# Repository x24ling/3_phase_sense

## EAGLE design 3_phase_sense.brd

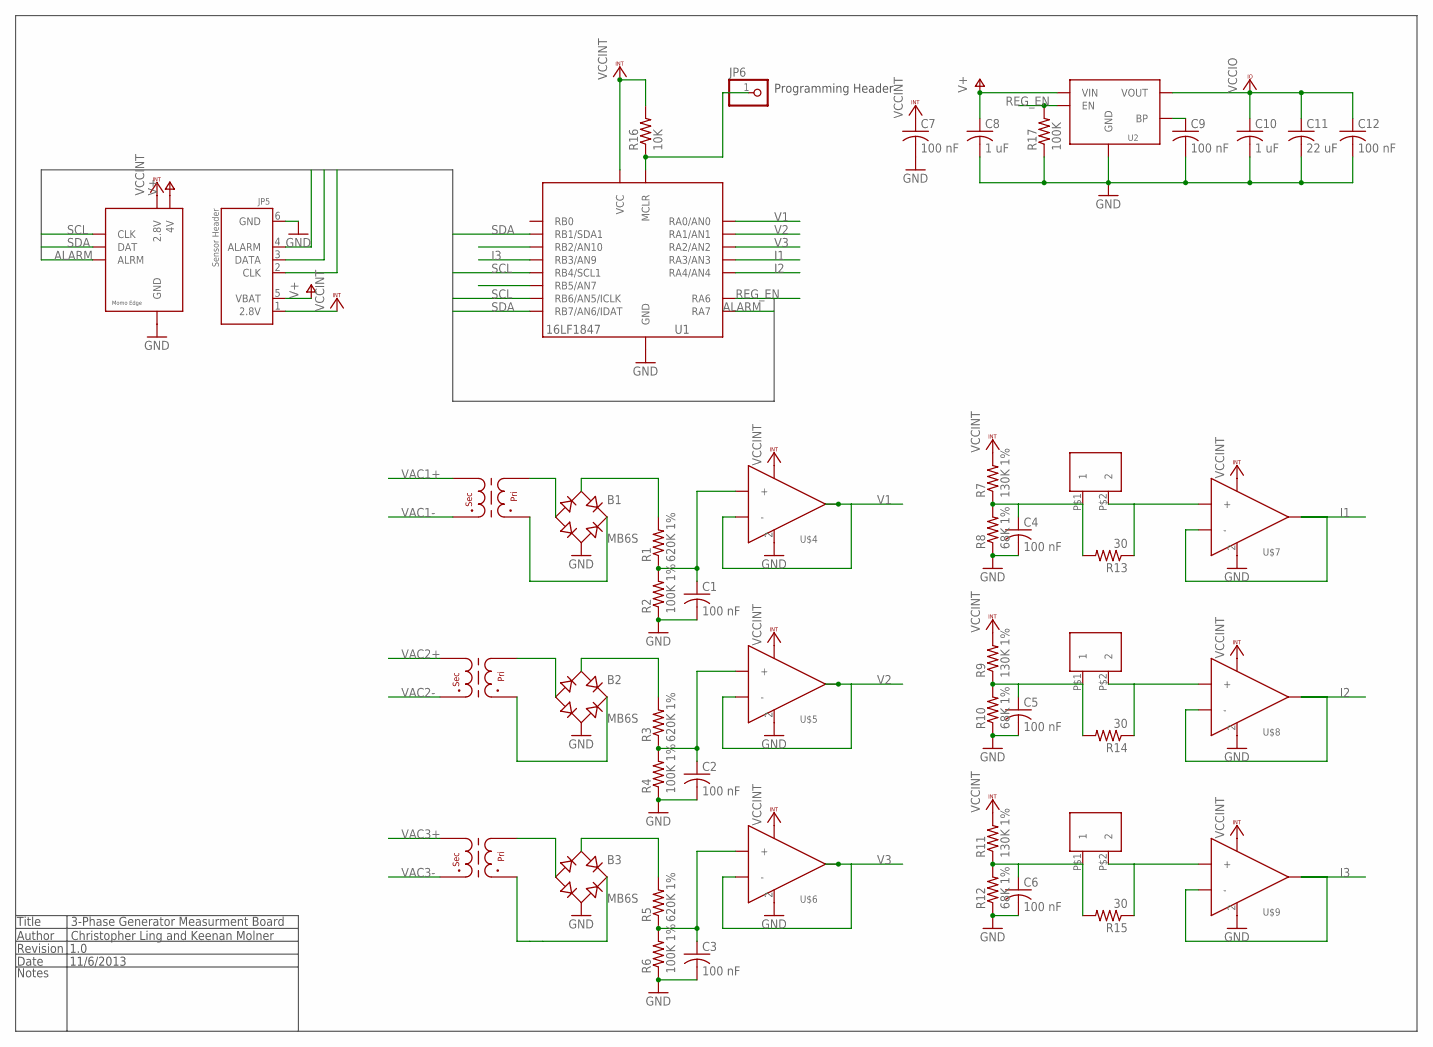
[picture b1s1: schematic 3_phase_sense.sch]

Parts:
B1, B2, B3: MB6S; SOIC-4
C1, C2, C3, C4, C5, C6, C7, C9, C12: 100 nF; C0402K; DIGIKEY-PN 445-1265-1-ND
C8, C10: 1 uF; C0402K; DIGIKEY-PN 445-4114-1-ND
C11: 22 uF; C1206K; DIGIKEY-PN 478-3865-1-ND
JP1, JP2, JP3: 5MM-SCREWTERM-2POS; 5MM-SCREWTERM
JP4: MOMO-VERT-6M; 1X06; DIGIKEY-PN S7004-ND
JP5: MOMO-SENSOR-RJ11; RJ-12
JP6: PINHD-1X1; 1X01
R1, R3, R5: 620K 1%; R0603; DIGIKEY-PN P620KHCT-ND
R2, R4, R6: 100K 1%; R0603; DIGIKEY-PN P100KHCT-ND
R7, R9, R11: 130K 1%; R0603; DIGIKEY-PN P620KHCT-ND
R8, R10, R12: 68K 1%; R0603; DIGIKEY-PN P100KHCT-ND
R13, R14, R15: 30; R2512; DIGIKEY-PN CRF2512-FV-R001ELFCT-ND
R16: 10K; R0603; DIGIKEY-PN P10.0KHCT-ND
R17: 100K; R0603; DIGIKEY-PN P100KHCT-ND
U1: PIC1847; SSOP20
U2: AP7115-LDO; SOT353
U$1, U$2, U$3: CJ5143-AL
U$4, U$5, U$6, U$7, U$8, U$9: NJU7011F; SOT23-5L

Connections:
ALARM: JP4.5 (ALRM), JP5.4 (ALARM), U1.17 (RA7)
GND: B1.~2 (AC2), B2.~2 (AC2), B3.~2 (AC2), C1.2, C2.2, C3.2, C4.2, C5.2, C6.2, C7.2, C8.2, C9.2, C10.2, C11.2, C12.2, JP4.7 (GND), JP5.6 (GND), R2.1, R4.1, R6.1, R8.1, R10.1, R12.1, R17.1, U1.15 (GND), U1.16 (GND), U2.2 (GND), U$4.2 (VSS), U$5.2 (VSS), U$6.2 (VSS), U$7.2 (VSS), U$8.2 (VSS), U$9.2 (VSS)
I1: U1.2 (RA3/AN3), U$7.3 (-), U$7.5 (OUT)
I2: U1.3 (RA4/AN4), U$8.3 (-), U$8.5 (OUT)
I3: U1.10 (RB3/AN9), U$9.3 (-), U$9.5 (OUT)
unnamed: C9.1, U2.4 (BP)
unnamed: JP6.1, R16.1, U1.4 (MCLR)
unnamed: JP1.P$2 (2), R13.1, U$7.1 (+)
unnamed: JP2.P$2 (2), R14.1, U$8.1 (+)
unnamed: B1.~1 (AC1), R1.2
unnamed: JP3.P$2 (2), R15.1, U$9.1 (+)
unnamed: B1.-, U$1.P$4
unnamed: B1.+, U$1.P$1
unnamed: B2.~1 (AC1), R3.2
unnamed: B2.-, U$2.P$4
unnamed: B2.+, U$2.P$1
unnamed: B3.~1 (AC1), R5.2
unnamed: B3.-, U$3.P$4
unnamed: B3.+, U$3.P$1
REG_EN: R17.2, U1.18 (RA6), U2.3 (EN)
SCL: JP4.3 (CLK), JP5.2 (CLK), U1.11 (RB4/SCL1), U1.13 (RB6/AN5/ICLK)
SDA: JP4.4 (DAT), JP5.3 (DATA), U1.8 (RB1/SDA1), U1.14 (RB7/AN6/IDAT)
V1: U1.19 (RA0/AN0), U$4.3 (-), U$4.5 (OUT)
V1_UNBUFF: C1.1, R1.1, R2.2, U$4.1 (+)
V1_UNBUFF1: C2.1, R3.1, R4.2, U$5.1 (+)
V1_UNBUFF2: C3.1, R5.1, R6.2, U$6.1 (+)
V2: C4.1, JP1.P$1 (1), R7.1, R8.2, R13.2, U1.20 (RA1/AN1), U$5.3 (-), U$5.5 (OUT)
V3: U1.1 (RA2/AN2), U$6.3 (-), U$6.5 (OUT)
V4: C5.1, JP2.P$1 (1), R9.1, R10.2, R14.2
V5: C6.1, JP3.P$1 (1), R11.1, R12.2, R15.2
V+: C8.1, JP4.6 (4V), JP5.5 (VBAT), U2.1 (VIN)
VAC1+: U$1.P$5
VAC1-: U$1.P$6
VAC2+: U$2.P$5
VAC2-: U$2.P$6
VAC3+: U$3.P$5
VAC3-: U$3.P$6
VCCINT: C7.1, JP4.1 (2.8V), JP5.1 (2.8V), R7.2, R9.2, R11.2, R16.2, U1.5 (VCC), U1.6 (VCC), U$4.4 (VDD), U$5.4 (VDD), U$6.4 (VDD), U$7.4 (VDD), U$8.4 (VDD), U$9.4 (VDD)
VCCIO: C10.1, C11.1, C12.1, U2.5 (VOUT)

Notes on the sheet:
Title
Author
Revision
Date
Notes
3-Phase Generator Measurment Board
Christopher Ling and Keenan Molner
1.0
11/6/2013
Programming Header

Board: 2 copper layers, 49 parts (0 on the bottom side), 33 nets, no tracks yet.

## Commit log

2014-03-13 First Commit
    Schematic and Board
